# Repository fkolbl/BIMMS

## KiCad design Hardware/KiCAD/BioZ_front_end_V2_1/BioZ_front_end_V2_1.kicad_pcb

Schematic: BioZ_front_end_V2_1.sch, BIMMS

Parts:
C1, C4, C10, C11, C12, C13, C14, C15, C16, C22, C24, C29, C30, C31, C32, C33, C34, C40, C41, C42, C43, C44, C46, C52, C53, C54, C55, C56, C62, C67, C68, C69, C70, C76, C77, C78, C81, C82, C83, C86, C87, C89, C91, C92, C93, C94, C95, C97, C98, C100, C102: 100nF; C_0603_1608Metric
C2: 100uF; CP_Radial_D8.0mm_P5.00mm
C3, C5: 30pF; C_0603_1608Metric
C6, C7, C8, C9, C17, C18, C19, C20, C21, C23, C25, C27, C28, C39, C45, C47, C48, C49, C50, C51, C61, C63, C64, C65, C66, C72, C73, C75, C79, C84, C85, C90, C101: 10uF; CP_EIA-3528-21_Kemet-B
C26: 4.7pF; C_0603_1608Metric
C35, C36, C37, C38, C71, C74, C96, C99: 1uF; C_0603_1608Metric
C57, C58: 10pF; C_0603_1608Metric
C59, C60: 1pF; C_0603_1608Metric
C80: 0.5pF; C_0603_1608Metric
C88: 4.7nF; C_0603_1608Metric
D1, D3, D4, D5, D9, D10, D12, D13, D18, D19, D28, D36: LED; LED_0603_1608Metric
D2: LED RED; LED_0603_1608Metric
D6, D7, D8, D11, D14, D15, D16, D17, D20, D21, D22, D23, D24, D25, D26, D27, D29, D30, D31, D32, D33, D34, D35: MBR0530; D_SOD-123
D37: LED Red; LED_0603_1608Metric
F1: 800mA; Fuse_1206_3216Metric_Pad1.42x1.75mm_HandSolder
J1: DC IN; BarrelJack_CUI_PJ-063AH_Horizontal
J2: JTAG; PinHeader_2x05_P1.27mm_Vertical_SMD
J3: Power; PinSocket_1x03_P2.54mm_Horizontal; MPN 640456-3; Digi-Key_PN A19470-ND
J4: CH2_PWR; PinHeader_2x02_P2.54mm_Vertical
J5: CH1_PWR; PinHeader_2x02_P2.54mm_Vertical
J6: EXT_stim; SMA_Amphenol_132291_Vertical
J7: CH2 IN+; SMA_Amphenol_132291_Vertical
J8: CH2 IN-; SMA_Amphenol_132291_Vertical
J9: CH1 IN+; SMA_Amphenol_132291_Vertical
J10: CH1 IN-; SMA_Amphenol_132291_Vertical
J11: CH2 Output Con; PinSocket_2x03_P2.54mm_Horizontal
J12: CH1 Output Con; PinSocket_2x03_P2.54mm_Horizontal
J13: CH2 Input Con; PinSocket_1x04_P2.54mm_Horizontal
J14: CH1 Input Con; PinSocket_1x04_P2.54mm_Horizontal
J15: STIM_PWR; PinHeader_2x02_P2.54mm_Vertical
J16: EXT_Stim; PinHeader_1x02_P2.54mm_Vertical
J17: USB_C_Receptacle_USB2.0; USB_C_Receptacle_XKB_U262-16XN-4BVC11
J18: STM32 IO; PinHeader_2x07_P2.54mm_Horizontal
J19: Vmes+; SMA_Amphenol_132291_Vertical
J20: Vmes-; SMA_Amphenol_132291_Vertical
J21: Stim-; SMA_Amphenol_132291_Vertical
J22: Stim+; SMA_Amphenol_132291_Vertical
J23: Load; Molex_KK-254_AE-6410-04A_1x04_P2.54mm_Vertical
J24: Load2; PinSocket_1x04_P2.54mm_Horizontal
J25, J28: Scope 1; SMA_Amphenol_132291_Vertical
J26, J31: Scope 2; SMA_Amphenol_132291_Vertical
J27: AWG1; SMA_Amphenol_132291_Vertical
J29: AD2 EXT Conn; PinHeader_2x15_P2.54mm_Vertical
J30: AWG2; SMA_Amphenol_132291_Vertical
J32: AD2 Conn; PinSocket_2x15_P2.54mm_Horizontal
J33: UART; PinHeader_1x06_P2.54mm_Horizontal
JP3, JP4: GND; PinHeader_1x02_P2.54mm_Vertical
K1, K2, K3, K4, K5, K6, K7, K8, K9, K10, K11, K12, K13, K14, K15, K16, K17, K18, K19, K20, K21, K22, K23: EE2-5NUH-L
L1, L2, L3: 10uH; L_1210_3225Metric_Pad1.42x2.65mm_HandSolder
Q1, Q2, Q3, Q4, Q5, Q6, Q7, Q8, Q9, Q10, Q11, Q12, Q13, Q14, Q15, Q18, Q19, Q20, Q21, Q22, Q23, Q24, Q25: CPH3462
Q26, Q27: PMT200EPEX; SOT-223-3_TabPin2
R1, R4, R5, R9, R16, R18, R20, R21, R24, R25, R35, R44, R45, R48, R49, R52, R53, R63, R65, R69, R70, R74, R76, R80, R82, R84, R87, R89, R91, R94, R96, R97, R100, R101, R103, R105: 10k; R_0603_1608Metric
R2, R3, R8, R107, R108: 2k; R_0603_1608Metric
R6, R7, R26, R29, R30, R33, R40, R41, R46, R47, R59, R62: 4k7; R_0603_1608Metric
R10, R22, R23, R37, R50, R51, R64, R66, R71, R72, R73, R77, R78, R79, R83, R88, R90, R92, R95, R98, R99, R102, R104, R106: 100R; R_0603_1608Metric
R11: 1k8; R_0603_1608Metric
R12, R38, R39, R56, R58, R75: 1k; R_0603_1608Metric
R13, R14, R15, R17: 10M; R_0603_1608Metric
R19: 1k2; R_0603_1608Metric
R27, R28, R31, R32, R60, R61: 39k; R_0603_1608Metric
R34, R36, R42, R43: 390R; R_0603_1608Metric
R54, R55: 10R; R_0603_1608Metric
R57: 1M; R_0603_1608Metric
R67, R68: 5k1; R_0603_1608Metric
R81: 27R; R_0603_1608Metric
R93: 3k3; R_0603_1608Metric
R109: 47k; R_0603_1608Metric
RV1: 10k; Potentiometer_Bourns_3214J_Horizontal
RV2: 47k; Potentiometer_Bourns_3214J_Horizontal
SW1, SW2, SW3: SW_Push; SW_SPST_TL3305A
U1: TDN 5-0923WI; TDN 5-0910WI
U2: OPA192IDR; SOIC127P599X175-8N
U3, U4, U13: LT1962; MSOP-8_3x3mm_P0.65mm
U5, U6, U14: LT1964-BYP; TSOT-23-5
U7, U15: THS4631D; SOIC127P599X175-8N
U8, U9, U11, U12: AD8250; SOP50P490X110-10N
U10: THS4151IDGK
U16: LTC4416EMS#PBF; MSOP-10_MS; MANUFACTURER_PART_NUMBER ltc4416ims1
U17, U18: AD830; SOIC127P600X175-8N
U19: TEC_3-0911; TEC 3-0910
U20: STM32F103R4Tx; LQFP-64_10x10mm_P0.5mm
U21: TLV70233_SOT23-5; SOT-23-5
Y1: 16 MHz; Crystal_SMD_3225-4Pin_3.2x2.5mm_HandSoldering

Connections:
4_2_wires_+_COM: R96.1, R98.2, U20.4 (PC15)
4_2_wires_-_COM: R103.1, R104.2, U20.3 (PC14)
+5VA: C100.1, D6.1 (K), D7.1 (K), D8.1 (K), D11.1 (K), D14.1 (K), D15.1 (K), D16.1 (K), D17.1 (K), D20.1 (K), D21.1 (K), D22.1 (K), D23.1 (K), D24.1 (K), D25.1 (K), D26.1 (K), D27.1 (K), D29.1 (K), D30.1 (K), D31.1 (K), D32.1 (K), D33.1 (K), D34.1 (K), D35.1 (K), K1.1, K2.1, K3.1, K4.1, K5.1, K6.1, K7.1, K8.1, K9.1, K10.1, K11.1, K12.1, K13.1, K14.1, K15.1, K16.1, K17.1, K18.1, K19.1, K20.1, K21.1, K22.1, K23.1, L3.2, R93.1, U21.1 (IN), U21.3 (EN)
+12V: J3.3, J4.2, J5.2, J15.2, L2.2, R7.2
+14V5_CH1: C25.1, C32.1, C44.1, C48.1, C53.1, C64.1, C70.1, R32.1, R41.2, U4.1 (OUT), U9.8 (+VS), U12.8 (+VS)
+14V5_CH2: C23.1, C31.1, C42.1, C47.1, C52.1, C63.1, C68.1, R28.1, R40.2, U3.1 (OUT), U8.8 (+VS), U11.8 (+VS)
+14V5_stim: C9.1, C39.1, C40.1, C61.1, C62.1, C73.1, C77.1, C83.1, C84.1, C86.1, C89.1, C93.1, C97.1, R61.1, R67.2, U2.7 (V+), U7.7 (VS+), U10.3 (VCC+), U13.1 (OUT), U15.7 (VS+), U17.8 (VP), U18.8 (VP)
-12V: J3.1, J4.1, J5.1, J15.1, L1.2, R6.2
-14V5_stim: C45.2, C46.1, C51.2, C56.1, C79.2, C81.1, C82.2, C85.2, C87.1, C90.2, C92.1, C95.1, C98.1, R60.2, R68.2, U2.4 (-V), U7.4 (VS-), U10.6 (VCC-), U14.5 (VOUT), U15.4 (VS-), U17.5 (VN), U18.5 (VN)
/AD2_err: D37.2 (A), J29.26, J32.6
/AD2_status: D36.2 (A), J29.24, J32.8
/NRST: C94.2, J2.10, R101.2, SW3.1, U20.7 (NRST)
/PA0: J18.2, U20.14 (PA0)
/PA1: J18.3, U20.15 (PA1)
/PA2: J18.4, U20.16 (PA2)
/PA3: J18.5, U20.17 (PA3)
/PA8: J18.6, U20.41 (PA8)
/PA11: J18.7, U20.44 (PA11)
/PA12: J18.8, U20.45 (PA12)
/PA15: J18.9, U20.50 (PA15)
/PC6: J18.13, U20.37 (PC6)
/PC7: J18.12, U20.38 (PC7)
/PC8: J18.11, U20.39 (PC8)
/SPI_MISO: J29.22, J32.10, U20.22 (PA6)
/SPI_MOSI: J29.20, J32.12, U20.23 (PA7)
/SPI_NSS: J29.16, J32.16, U20.20 (PA4)
/SPI_SCK: J29.18, J32.14, U20.21 (PA5)
/SW1_uC: C4.2, R4.2, SW2.1, U20.11 (PC3)
/SW2_uC: C1.2, R1.2, SW1.1, U20.10 (PC2)
/SWCLK: J2.4, U20.49 (PA14)
/SWDIO: J2.2, U20.46 (PA13)
/UART_RX: J33.4, U20.43 (PA10)
/UART_TX: J33.3, U20.42 (PA9)
/uC_error: D2.2 (A), U20.8 (PC0)
/uC_state: D1.2 (A), U20.9 (PC1)
A0_0: J12.1, J29.15, J32.15, R21.2, U9.4 (A0)
A0_1: J12.5, J29.19, J32.11, R49.2, U12.4 (A0)
A0_2: J11.1, J29.23, J32.7, R20.2, U8.4 (A0)
A0_3: J11.5, J29.27, J32.3, R48.2, U11.4 (A0)
A1_0: J12.3, J29.17, J32.13, R25.2, U9.5 (A1)
A1_1: J12.6, J29.21, J32.9, R53.2, U12.5 (A1)
A1_2: J11.3, J29.25, J32.5, R24.2, U8.5 (A1)
A1_3: J11.6, J29.29, J32.1, R52.2, U11.5 (A1)
AWG1: J27.1 (In), J29.10, J32.22, K4.3 (2)
AWG2: J29.9, J30.1 (In), J32.21
CH1_coupling_COM: R18.1, R23.2, U20.26 (PB0)
CH1_output_COM: R45.1, R51.2, U20.27 (PB1)
CH2_coupling_COM: R16.1, R22.2, U20.28 (PB2)
CH2_output_COM: R44.1, R50.2, U20.55 (PB3)
Current_source_gain_COM: R5.1, R73.2, U20.33 (PB12)
Current_source_in_COM: R76.1, R78.2, U20.30 (PB11)
DC_FB_COM: R9.1, R10.2, U20.56 (PB4)
DC_offset: K1.4 (3), U10.2 (VOCM)
DC_sense: C96.1, K1.5 (4), K17.5 (4), K20.8 (5), K21.5 (4), K23.5 (4)
EXT_stim: J6.1 (In), J16.2, K4.5 (4)
GND: C1.1, C2.2, C3.1, C4.1, C5.1, C6.1, C7.2, C8.2, C9.2, C10.2, C11.2, C12.2, C13.1, C14.1, C15.1, C16.1, C17.2, C18.2, C19.2, C20.1, C21.1, C22.2, C23.2, C24.2, C25.2, C26.2, C27.1, C28.1, C29.2, C30.2, C31.2, C32.2, C33.2, C34.2, C39.2, C40.2, C45.1, C46.2, C47.2, C48.2, C49.1, C50.1, C51.1, C52.2, C53.2, C54.2, C55.2, C56.2, C57.2, C58.2, C61.2, C62.2, C63.2, C64.2, C65.1, C66.1, C67.2, C68.2, C69.2, C70.2, C72.2, C73.2, C75.1, C76.2, C77.2, C78.2, C79.1, C81.2, C84.2, C85.1, C86.2, C87.2, C89.2, C90.1, C91.2, C92.2, C93.2, C94.1, C95.2, C97.2, C98.2, C100.2, C101.2, C102.2, D3.2 (A), D4.1 (K), D5.1 (K), D9.1 (K), D10.1 (K), D12.2 (A), D13.2 (A), D18.1 (K), D19.2 (A), D28.1 (K), J1.2, J2.3, J2.5, J2.9, J3.2, J6.2 (Ext), J7.2 (Ext), J8.2 (Ext), J9.2 (Ext), J10.2 (Ext), J11.4, J12.4, J13.2, J13.3, J14.2, J14.3, J16.1, J17.A1 (GND), J17.A12 (GND), J17.B1 (GND), J17.B12 (GND), J17.S1 (SHIELD), J18.14, J19.2 (Ext), J20.2 (Ext), J21.2 (Ext), J22.2 (Ext), J25.2 (Ext), J26.2 (Ext), J27.2 (Ext), J28.2 (Ext), J29.5, J29.6, J29.11, J29.12, J30.2 (Ext), J31.2 (Ext), J32.19, J32.20, J32.25, J32.26, J33.2, JP3.2, JP4.2, K1.3 (2), K5.8 (5), K6.8 (5), K7.3 (2), K12.3 (2), K12.10 (7), K13.5 (4), K13.8 (5), K18.4 (3), Q1.3 (S), Q2.3 (S), Q3.3 (S), Q4.3 (S), Q5.3 (S), Q6.3 (S), Q7.3 (S), Q8.3 (S), Q9.3 (S), Q10.3 (S), Q11.3 (S), Q12.3 (S), Q13.3 (S), Q14.3 (S), Q15.3 (S), Q18.3 (S), Q19.3 (S), Q20.3 (S), Q21.3 (S), Q22.3 (S), Q23.3 (S), Q24.3 (S), Q25.3 (S), R2.2, R3.2, R5.2, R9.2, R12.1, R13.1, R14.1, R15.1, R16.2, R17.1, R18.2, R20.1, R21.1, R24.1, R25.1, R26.1, R29.2, R30.1, R33.2, R35.2, R36.1, R44.2, R45.2, R48.1, R49.1, R52.1, R53.1, R57.2, R59.1, R62.2, R63.2, R65.2, R69.2, R70.2, R74.2, R76.2, R82.2, R84.2, R87.2, R89.2, R91.2, R94.2, R96.2, R97.2, R100.2, R103.2, R105.2, R107.2, R108.2, SW1.2, SW2.2, SW3.2, U1.2 (-VINGND), U1.6 (GND), U3.4 (GND), U4.4 (GND), U5.1 (GND), U6.1 (GND), U8.2 (DGND), U8.9 (REF), U9.2 (DGND), U9.9 (REF), U11.1 (-IN), U11.2 (DGND), U11.9 (REF), U12.1 (-IN), U12.2 (DGND), U12.9 (REF), U13.4 (GND), U14.1 (GND), U16.3 (GND), U16.4 (*E2), U18.1 (X1), U18.3 (Y1), U19.1 (-VINGND), U19.7 (-VOUT), U20.12 (VSSA), U20.18 (VSS), U20.31 (VSS), U20.47 (VSS), U20.60 (BOOT0), U20.63 (VSS), U21.2 (GND)
Gain_CS_IN: R75.2, R109.2, U17.4 (Y2), U17.7 (OUT)
Gain_CS_OUT: K11.4 (3), K21.4 (3), U17.3 (Y1), U18.2 (X2)
I+_2_stim+_COM: R100.1, R102.2, U20.35 (PB14)
I-_2_stim-_COM: R87.1, R88.2, U20.40 (PC9)
IO6: J29.28, J32.4
IO7: J29.30, J32.2
I_load: C74.2, K10.3 (2), K16.4 (3)
I_load-: C71.2, K7.4 (3), K10.10 (7)
I_load-_Cout: C71.1, K8.9 (6), K10.9 (6), R56.1, R57.1, U15.3 (VIN+)
I_load_Cout: C74.1, C80.2, K10.4 (3), R56.2, R58.1, U15.2 (VIN-)
Iin+: K13.4 (3), U17.1 (X1)
Iin-: K13.9 (6), U17.2 (X2)
Istim-: K9.5 (4), K15.4 (3), U18.4 (Y2), U18.7 (OUT)
unnamed: C3.2, U20.5 (PD0), Y1.1
unnamed: C5.2, U20.6 (PD1), Y1.2
unnamed: C6.2, C10.1, L1.1, U1.5 (-VOUT)
unnamed: C7.1, C11.1, L2.1, U1.7 (+VOUT)
unnamed: C8.1, C12.1, L3.1, U19.6 (+VOUT)
unnamed: C18.1, C22.1, J4.4, U3.5 (~SHDN), U3.8 (IN)
unnamed: C19.1, C24.1, J5.4, U4.5 (~SHDN), U4.8 (IN)
unnamed: C20.2, C29.1, J4.3, U5.2 (VIN)
unnamed: C21.2, C30.1, J5.3, U6.2 (VIN)
unnamed: C26.1, R11.1, U7.3 (VIN+)
unnamed: C41.1, U5.3 (BYP)
unnamed: C42.2, U3.3 (BYP)
unnamed: C43.1, U6.3 (BYP)
unnamed: C44.2, U4.3 (BYP)
unnamed: C57.1, R38.2, U11.10 (+IN)
unnamed: C58.1, R39.2, U12.10 (+IN)
unnamed: C59.1, R34.2, R42.1, U10.8 (VIN+)
unnamed: C59.2, R42.2, R55.1, U10.5 (VOUT-)
unnamed: C60.1, R36.2, R43.1, U10.1 (VIN-)
unnamed: C60.2, R43.2, R54.1, U10.4 (VOUT+)
unnamed: C72.1, C76.1, J15.4, U13.5 (~SHDN), U13.8 (IN)
unnamed: C75.2, C78.1, J15.3, U14.2 (VIN)
unnamed: C80.1, R58.2, R79.1, U15.6 (VOUT-)
unnamed: C82.1, U14.3 (BYP)
unnamed: C83.2, U13.3 (BYP)
unnamed: C88.2, R80.1, U2.2 (-IN)
unnamed: C91.1, R81.2
unnamed: D1.1 (K), R2.1
unnamed: D2.1 (K), R3.1
unnamed: D3.1 (K), R6.1
unnamed: D4.2 (A), R7.1
unnamed: D5.2 (A), R8.2
unnamed: D6.2 (A), K1.12 (8), Q1.1 (D)
unnamed: D7.2 (A), K2.12 (8), Q2.1 (D)
unnamed: D8.2 (A), K3.12 (8), Q3.1 (D)
unnamed: D9.2 (A), R40.1
unnamed: D10.2 (A), R41.1
unnamed: D11.2 (A), K4.12 (8), Q4.1 (D)
unnamed: D12.1 (K), R46.1
unnamed: D13.1 (K), R47.1
unnamed: D14.2 (A), K5.12 (8), Q5.1 (D)
unnamed: D15.2 (A), K6.12 (8), Q6.1 (D)
unnamed: D16.2 (A), K7.12 (8), Q7.1 (D)
unnamed: D17.2 (A), K8.12 (8), Q8.1 (D)
unnamed: D18.2 (A), R67.1
unnamed: D19.1 (K), R68.1
unnamed: D20.2 (A), K9.12 (8), Q9.1 (D)
unnamed: D21.2 (A), K10.12 (8), Q10.1 (D)
unnamed: D22.2 (A), K11.12 (8), Q11.1 (D)
unnamed: D23.2 (A), K12.12 (8), Q12.1 (D)
unnamed: D24.2 (A), K13.12 (8), Q13.1 (D)
unnamed: D25.2 (A), K14.12 (8), Q14.1 (D)
unnamed: D26.2 (A), K15.12 (8), Q15.1 (D)
unnamed: D27.2 (A), K16.12 (8), Q18.1 (D)
unnamed: D28.2 (A), R93.2
unnamed: D29.2 (A), K17.12 (8), Q19.1 (D)
unnamed: D30.2 (A), K18.12 (8), Q20.1 (D)
unnamed: D31.2 (A), K19.12 (8), Q21.1 (D)
unnamed: D32.2 (A), K20.12 (8), Q22.1 (D)
unnamed: D33.2 (A), K21.12 (8), Q23.1 (D)
unnamed: D34.2 (A), K22.12 (8), Q24.1 (D)
unnamed: D35.2 (A), K23.12 (8), Q25.1 (D)
unnamed: D36.1 (K), R107.1
unnamed: D37.1 (K), R108.1
unnamed: F1.2, Q26.3 (S), Q27.3 (S), U16.8 (VS)
unnamed: K7.5 (4), K9.4 (3)
unnamed: K8.5 (4), R84.1
unnamed: K11.3 (2), RV1.1, RV1.2
unnamed: K11.5 (4), RV2.1, RV2.2
unnamed: Q1.2 (G), R10.1
unnamed: Q2.2 (G), R22.1
unnamed: Q3.2 (G), R23.1
unnamed: Q4.2 (G), R37.1
unnamed: Q5.2 (G), R50.1
unnamed: Q6.2 (G), R51.1
unnamed: Q7.2 (G), R64.1
unnamed: Q8.2 (G), R66.1
unnamed: Q9.2 (G), R71.1
unnamed: Q10.2 (G), R72.1
unnamed: Q11.2 (G), R73.1
unnamed: Q12.2 (G), R77.1
unnamed: Q13.2 (G), R78.1
unnamed: Q14.2 (G), R83.1
unnamed: Q15.2 (G), R88.1
unnamed: Q18.2 (G), R90.1
unnamed: Q19.2 (G), R92.1
unnamed: Q20.2 (G), R95.1
unnamed: Q21.2 (G), R98.1
unnamed: Q22.2 (G), R99.1
unnamed: Q23.2 (G), R102.1
unnamed: Q24.2 (G), R104.1
unnamed: Q25.2 (G), R106.1
unnamed: Q26.1 (G), U16.10 (G1)
unnamed: Q27.1 (G), U16.6 (G2)
unnamed: R12.2, R19.1, U7.2 (VIN-)
unnamed: R26.2, R27.1, U5.4 (ADJ)
unnamed: R28.2, R29.1, U3.2 (ADJ)
unnamed: R30.2, R31.1, U6.4 (ADJ)
unnamed: R32.2, R33.1, U4.2 (ADJ)
unnamed: R38.1, U8.7 (OUT)
unnamed: R39.1, U9.7 (OUT)
unnamed: R59.2, R60.1, U14.4 (ADJ)
unnamed: R61.2, R62.1, U13.2 (ADJ)
unnamed: R75.1, RV1.3
unnamed: R109.1, RV2.3
PWR+: J29.8, J32.24
PWR-: J29.7, J32.23
STIM+_coupling: C96.2, J22.1 (In), J23.1, J24.4, K19.5 (4), K20.9 (6)
STIM-: C99.1, K14.5 (4), K15.5 (4), K16.5 (4), K18.5 (4), K20.5 (4)
STIM-_coupling: C99.2, J21.1 (In), J23.4, J24.1, K20.4 (3), K22.5 (4)
STIM_INPUT_COM: R35.1, R37.2, U20.57 (PB5)
TIA+: K8.4 (3), R79.2
TIA_2_CH2_COM: R65.1, R66.2, U20.61 (PB8)
TIA_Select_1_COM: R63.1, R64.2, U20.58 (PB6)
TIA_Select_2_COM: R69.1, R71.2, U20.59 (PB7)
TIA_coupling_COM: R70.1, R72.2, U20.62 (PB9)
TR1: J29.14, J32.18, U20.25 (PC5)
TR2: J29.13, J32.17, U20.24 (PC4)
V+_2_stim+_COM: R105.1, R106.2, U20.36 (PB15)
V-_2_stim-_COM: R82.1, R83.2, U20.51 (PC10)
VCC: C2.1, F1.1, U1.1 (+VINVCC), U19.2 (+VINVCC)
V_amp: K12.5 (4), R19.2, R34.1, U7.6 (VOUT-)
Vfb_volta: K12.9 (6), R80.2
Vin: K4.4 (3), R11.2
Vin+_ch1: C37.1, J9.1 (In), J14.1, J19.1 (In), J23.2, J24.3, K3.3 (2), K19.4 (3)
Vin+_ch2: C35.1, J7.1 (In), J13.1, K2.3 (2), K8.3 (2)
Vin-_ch1: C38.2, J10.1 (In), J14.4, J20.1 (In), J23.3, J24.2, K3.10 (7), K22.4 (3)
Vin-_ch2: C36.2, J8.1 (In), J13.4, K2.10 (7), K8.10 (7)
Vin_DC: J1.1, Q26.2 (D), U16.2 (E1), U16.9 (V1)
Vin_USB: J17.A4 (VBUS), J17.A9 (VBUS), J17.B4 (VBUS), J17.B9 (VBUS), Q27.2 (D), U16.7 (V2)
Vout+: K13.3 (2), K23.4 (3), R54.2
Vout-: K9.3 (2), K13.10 (7), K14.4 (3), R55.2
Vref_volta: K12.4 (3), U2.3 (+IN)
WE_REF: C88.1, K17.4 (3), R81.1, U2.6 (OUT)
ch1+_Cout: C37.2, K3.4 (3), R17.2, U9.10 (+IN)
ch1-_Cout: C38.1, K3.9 (6), R14.2, U9.1 (-IN)
ch1_out: J12.2, K6.5 (4), U12.7 (OUT)
ch2+_Cout: C35.2, K2.4 (3), R15.2, U8.10 (+IN)
ch2-_Cout: C36.1, K2.9 (6), R13.2, U8.1 (-IN)
ch2_out: J11.2, K5.5 (4), U11.7 (OUT)
gnd_2_stim-_COM: R94.1, R95.2, U20.53 (PC12)
scope1+: J28.1 (In), J29.2, J32.30, K6.4 (3), K12.8 (5)
scope1-: J25.1 (In), J29.1, J32.29, JP3.1, K6.9 (6)
scope2+: J29.4, J31.1 (In), J32.28, K5.4 (3)
scope2-: J26.1 (In), J29.3, J32.27, JP4.1, K5.9 (6)
stim_coupling_COM: R97.1, R99.2, U20.2 (PC13)
tia_2_stim-_COM: R89.1, R90.2, U20.52 (PC11)
volta_2_stim+_COM: R91.1, R92.2, U20.34 (PB13)
volta_EN_COM: R74.1, R77.2, U20.29 (PB10)

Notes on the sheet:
STM32F103
STLink Prog Connector
STM32 Status LEDs
Tactile SWITCHES
Voltage source
TIA
Stim LDOs
Fcut = 19 MHz
G = 2.2
Current Source
Potentiostat FB
Power Supply
STIM + Sel
STIM - Sel
Stim Coupling
4 - 2 wires mode
Electrode Conn
AD2 Conn
Fcut = 16 MHz
Channel 1
Channel 2

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
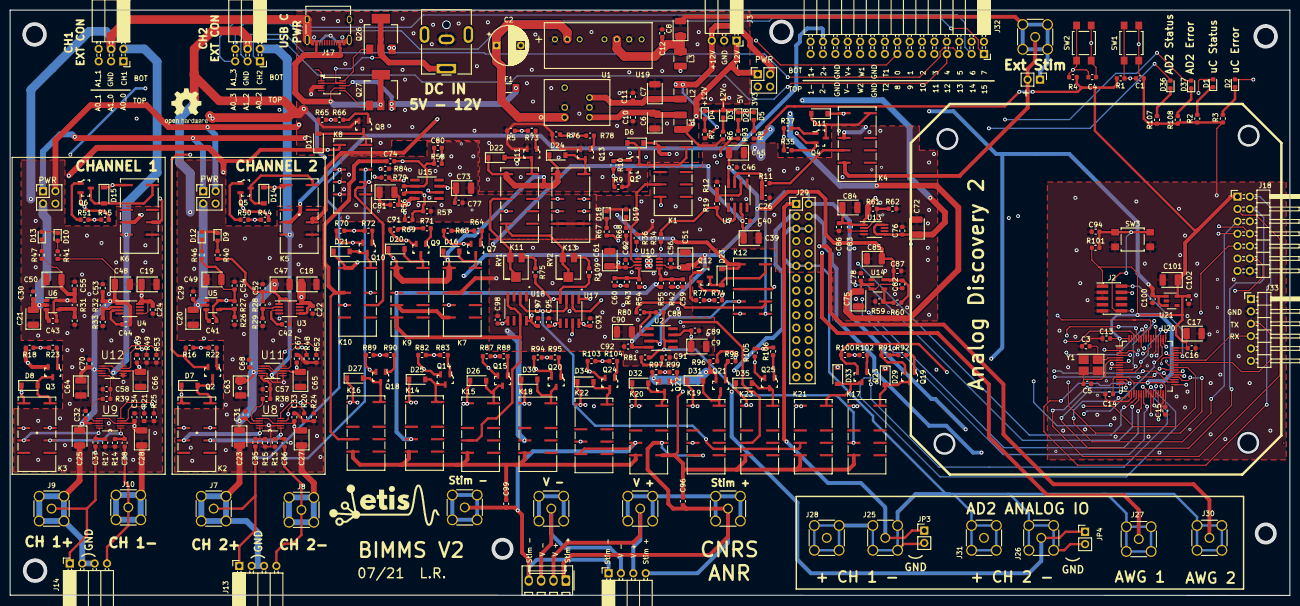
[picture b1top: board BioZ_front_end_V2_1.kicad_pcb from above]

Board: 4 copper layers, 262.5 x 120.1 mm, 360 parts (0 on the bottom side), 220 nets.

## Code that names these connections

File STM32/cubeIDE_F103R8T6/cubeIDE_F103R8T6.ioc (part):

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Mcu.Name=STM32F103R(8-B)Tx
Mcu.Package=LQFP64
Mcu.UserName=STM32F103R8Tx
PA13.Mode=Serial_Wire
PA13.Signal=SYS_JTMS-SWDIO
PA14.Mode=Serial_Wire
PA14.Signal=SYS_JTCK-SWCLK
PA4.GPIOParameters=GPIO_PuPd,GPIO_Label,GPIO_ModeDefaultEXTI
PA4.GPIO_Label=SS
PA4.GPIO_ModeDefaultEXTI=GPIO_MODE_IT_FALLING
PA4.GPIO_PuPd=GPIO_PULLUP
PA4.Signal=GPXTI4
PA5.Mode=Full_Duplex_Slave
PA5.Signal=SPI1_SCK
PA6.Mode=Full_Duplex_Slave
PA6.Signal=SPI1_MISO
PA7.Mode=Full_Duplex_Slave
PA7.Signal=SPI1_MOSI
PB0.GPIOParameters=GPIO_Label
PB0.GPIO_Label=relay1
PB0.Signal=GPIO_Output
PB1.GPIOParameters=GPIO_Label
PB1.GPIO_Label=relay2
PB1.Signal=GPIO_Output
PB10.GPIOParameters=GPIO_Label
PB10.GPIO_Label=relay11
PB10.Signal=GPIO_Output
PB11.GPIOParameters=GPIO_Label
PB11.GPIO_Label=relay12
PB11.Signal=GPIO_Output
PB12.GPIOParameters=GPIO_Label
PB12.GPIO_Label=relay13
PB12.Signal=GPIO_Output
PB13.GPIOParameters=GPIO_Label
PB13.GPIO_Label=relay14
PB13.Signal=GPIO_Output
PB14.GPIOParameters=GPIO_Label
PB14.GPIO_Label=relay15
PB14.Signal=GPIO_Output
PB15.GPIOParameters=GPIO_Label
PB15.GPIO_Label=relay16
PB15.Signal=GPIO_Output
PB2.GPIOParameters=GPIO_Label
PB2.GPIO_Label=relay3
PB2.Signal=GPIO_Output
PB3.GPIOParameters=GPIO_Label
PB3.GPIO_Label=relay4
PB3.Signal=GPIO_Output
PB4.GPIOParameters=GPIO_Label
PB4.GPIO_Label=relay5
PB4.Signal=GPIO_Output
PB5.GPIOParameters=GPIO_Label
PB5.GPIO_Label=relay6
PB5.Signal=GPIO_Output
PB6.GPIOParameters=GPIO_Label
PB6.GPIO_Label=relay7
PB6.Signal=GPIO_Output
PB7.GPIOParameters=GPIO_Label
PB7.GPIO_Label=relay8
PB7.Signal=GPIO_Output
PB8.GPIOParameters=GPIO_Label
PB8.GPIO_Label=relay9
PB8.Signal=GPIO_Output
PB9.GPIOParameters=GPIO_Label
PB9.GPIO_Label=relay10
PB9.Signal=GPIO_Output
PC0.GPIOParameters=GPIO_Label
PC0.GPIO_Label=errorLED
PC0.Signal=GPIO_Output
PC1.GPIOParameters=GPIO_Label
PC1.GPIO_Label=statusLED
PC1.Signal=GPIO_Output
PC10.GPIOParameters=GPIO_Label
PC10.GPIO_Label=relay18
PC10.Signal=GPIO_Output
PC11.GPIOParameters=GPIO_Label
PC11.GPIO_Label=relay19
PC11.Signal=GPIO_Output
PC12.GPIOParameters=GPIO_Label
PC12.GPIO_Label=relay20
PC12.Signal=GPIO_Output
PC13-TAMPER-RTC.GPIOParameters=GPIO_Label
PC13-TAMPER-RTC.GPIO_Label=relay21
PC13-TAMPER-RTC.Signal=GPIO_Output
PC14-OSC32_IN.GPIOParameters=GPIO_Label
PC14-OSC32_IN.GPIO_Label=relay22
PC14-OSC32_IN.Signal=GPIO_Output
PC15-OSC32_OUT.GPIOParameters=GPIO_Label
PC15-OSC32_OUT.GPIO_Label=relay23
PC15-OSC32_OUT.Signal=GPIO_Output
PC2.GPIOParameters=GPIO_Label
PC2.GPIO_Label=SW1
PC2.Signal=GPIO_Input
PC3.GPIOParameters=GPIO_Label
PC3.GPIO_Label=SW2
PC3.Signal=GPIO_Input
PC9.GPIOParameters=GPIO_Label
PC9.GPIO_Label=relay17
PC9.Signal=GPIO_Output
PD0-OSC_IN.Mode=HSE-External-Clock-Source
PD0-OSC_IN.Signal=RCC_OSC_IN
PD1-OSC_OUT.Mode=HSE-External-Clock-Source
PD1-OSC_OUT.Signal=RCC_OSC_OUT
RCC.SYSCLKFreq_VALUE=72000000
RCC.SYSCLKSource=RCC_SYSCLKSOURCE_PLLCLK
board=custom

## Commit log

2021-12-08 packaging bimms
2021-12-08 adding example script
2021-12-08 add hardware files
2021-12-08 fix commit
2021-12-08 add cubeIDE source files
2021-12-08 fix setup.py
2021-12-08 changed andi to Andi-py
2021-12-08 add toml file for PyPI upload
2021-12-09 add example scripts
2022-01-04 update files
2022-03-09 Add gain voltage and gain current
2022-03-09 fix IA gain bug
2022-12-01 Update BIMMS.py
    adding destructor to bimms
    +
    changing Gain_TIA value to correspond with the new resistor value
2023-07-13 Update BIMMS.py
    adding bimms init from Id or serial number.
    +
    adding keep_on, keep_off to keep or not the switch configuration after destruction
2023-07-13 Update constants.py
    adding BimmsSerialNumbers
2023-07-13 Create bash_bimms
2023-10-24 update constants
2023-10-24 Fix SPI CS com error
2023-10-24 change archi source
2023-11-05 black formated
2023-11-09 multiple structural changes
2023-11-10 ...multiple structural changes...
2023-11-13 Fix bugs in BIMMSConfig
2023-11-13 update hardware tests and BIMMSconfig
2023-11-14 fix BIMMSconf bug
2023-11-14 config_mode.__repr__
2023-11-14 adding config_mode_list + BIMMS_class for save
2023-11-14 Add measure methods
2023-11-14 Rename BIMMSHardware.py to BIMMShardware.py
2023-11-14 config_range +save/load config
2023-11-14 udpate bimms mesures
2023-11-14 change test 010 name
2023-11-14 update readme - removed unsed methods in BIMMSconfig
2023-11-14 comment unused parameters in BIMMShardware
2023-11-15 BIMMS test + BIMMS ad2
2023-11-15 update BIMMSad2
2023-11-15 Bimms calibration
2023-11-15 measure classes
2023-11-15 update measures
2023-11-16 print except error for debbug
2023-11-16 update test_CHANNEL_1_2 - fix bugs - update measures
2023-11-16 fix measures
2023-11-16 update test 002 Hardware
2023-11-16 update test 003 current source
2023-11-16 add test 004 TIA
2023-11-17 create Results_class - doesn't work yet
2023-11-17 bimms results
2023-11-17 results class
2023-11-17 adding __fixed_attr: allow to load new attributes
2023-11-17 test fixing
2023-11-21 remove print
2023-12-06 Update pyproject.toml
    version
2023-12-06 Update __init__.py
    version
2023-12-07 fix MANY bugs
2023-12-07 ignore test figures + setup.py
2023-12-07 test figures folder
2023-12-07 fix test 003b
2023-12-07 Update examples
2023-12-07 Update setup.py
    version change
2023-12-07 Update pyproject.toml
    version change
2023-12-07 Update __init__.py
    version change
2023-12-07 Add files via upload
    blanc json for python build success
2023-12-07 Add files via upload
    same as just before
2023-12-07 Update __init__.py
    don't use bash_bimms case
2023-12-07 fix cast config.config_settling
2023-12-07 Update setup.py
    version
2023-12-14 add STM32F103xxx code
2024-02-21 improve temporal_results postproc
2024-03-13 hardware update
2024-03-13 confige changes: "TEST" -> "MANUAL"
2024-06-04 modif config test -> Manual + EIS results
2024-06-04 pip install files
2024-06-04 Bump version: 1.1.2 → 1.1.3

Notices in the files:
parts and their libraries:
Copyright 2016 Accelerated Designs. All rights reserved.
